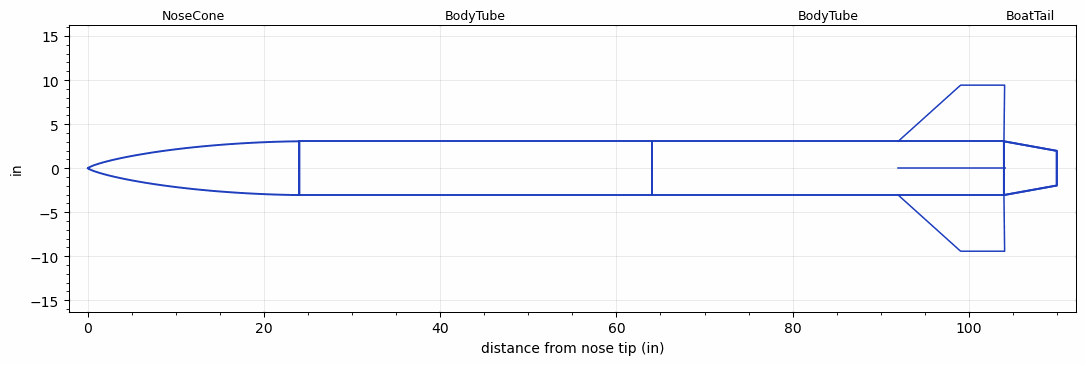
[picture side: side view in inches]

<RASAeroDocument>
 <FileVersion>2</FileVersion>
 <RocketDesign>
  <NoseCone>
   <Length>24</Length>
   <Diameter>6.1</Diameter>
   <Shape>LV-Haack</Shape>
   <Location>0</Location>
  </NoseCone>
  <BodyTube>
   <Length>40</Length>
   <Diameter>6.1</Diameter>
   <Location>24</Location>
  </BodyTube>
  <BodyTube>
   <Length>40</Length>
   <Diameter>6.1</Diameter>
   <RailGuideDiameter>0.372</RailGuideDiameter>
   <RailGuideHeight>0.078</RailGuideHeight>
   <Location>64</Location>
   <BoattailLength>6</BoattailLength>
   <BoattailRearDiameter>3.937</BoattailRearDiameter>
   <Fin>
    <Count>4</Count>
    <Chord>12.0078</Chord>
    <Span>6.3779</Span>
    <SweepDistance>7.0866</SweepDistance>
    <TipChord>5</TipChord>
    <Thickness>0.25</Thickness>
    <Location>12.0078</Location>
    <AirfoilSection>Single Wedge</AirfoilSection>
   </Fin>
  </BodyTube>
  <BoatTail>
   <Length>6</Length>
   <Diameter>6.1</Diameter>
   <RearDiameter>3.937</RearDiameter>
   <Location>104</Location>
  </BoatTail>
  <Surface>Smooth (Zero Roughness)</Surface>
  <ModifiedBarrowman>False</ModifiedBarrowman>
  <Turbulence>False</Turbulence>
  <UseBooster1>False</UseBooster1>
  <UseBooster2>False</UseBooster2>
 </RocketDesign>
 <LaunchSite>
  <Altitude>4595</Altitude>
  <Pressure>24.76</Pressure>
  <RodAngle>6</RodAngle>
  <RodLength>2.2</RodLength>
  <Temperature>56.84</Temperature>
  <WindSpeed>2.33</WindSpeed>
 </LaunchSite>
 <Recovery>
  <Altitude1>1000</Altitude1>
  <Altitude2>0</Altitude2>
  <DeviceType1>Parachute</DeviceType1>
  <DeviceType2>Parachute</DeviceType2>
  <Event1>True</Event1>
  <Event2>True</Event2>
  <Size1>24</Size1>
  <Size2>120</Size2>
  <EventType1>Apogee</EventType1>
  <EventType2>Apogee</EventType2>
  <CD1>0.97</CD1>
  <CD2>2.2</CD2>
 </Recovery>
 <MachAlt>
  <Item>0.02, 1980</Item>
  <Item>0.03, 1977</Item>
  <Item>0.04, 1</Item>
  <Item>0.04, 1973</Item>
  <Item>0.05, 1968</Item>
  <Item>0.06, 2</Item>
  <Item>0.06, 1963</Item>
  <Item>0.07, 3</Item>
  <Item>0.07, 1956</Item>
  <Item>0.08, 4</Item>
  <Item>0.08, 1947</Item>
  <Item>0.09, 1937</Item>
  <Item>0.1, 5</Item>
  <Item>0.1, 1928</Item>
  <Item>0.11, 1916</Item>
  <Item>0.12, 8</Item>
  <Item>0.12, 1903</Item>
  <Item>0.13, 1890</Item>
  <Item>0.14, 1877</Item>
  <Item>0.15, 1855</Item>
  <Item>0.17, 1828</Item>
  <Item>0.19, 1792</Item>
  <Item>0.2, 1769</Item>
  <Item>0.22, 1748</Item>
  <Item>0.23, 29</Item>
  <Item>0.23, 1726</Item>
  <Item>0.24, 1691</Item>
  <Item>0.25, 33</Item>
  <Item>0.27, 42</Item>
  <Item>0.28, 1622</Item>
  <Item>0.29, 1589</Item>
  <Item>0.32, 57</Item>
  <Item>0.33, 1507</Item>
  <Item>0.34, 1468</Item>
  <Item>0.35, 74</Item>
  <Item>0.36, 1415</Item>
  <Item>0.38, 1384</Item>
  <Item>0.39, 93</Item>
  <Item>0.4, 1332</Item>
  <Item>0.43, 114</Item>
  <Item>0.43, 1270</Item>
  <Item>0.49, 1125</Item>
  <Item>0.52, 1049</Item>
  <Item>0.55, 977</Item>
  <Item>0.56, 215</Item>
  <Item>0.58, 910</Item>
  <Item>0.61, 860</Item>
  <Item>0.63, 296</Item>
  <Item>0.63, 821</Item>
  <Item>0.66, 756</Item>
  <Item>0.69, 688</Item>
  <Item>0.71, 409</Item>
  <Item>0.72, 605</Item>
  <Item>0.73, 470</Item>
  <Item>0.73, 532</Item>
 </MachAlt>
 <SimulationList>
  <Simulation>
   <SustainerEngine>M1850W  (Aerotech)</SustainerEngine>
   <SustainerLaunchWt>47.52</SustainerLaunchWt>
   <SustainerNozzleDiameter>2.992</SustainerNozzleDiameter>
   <SustainerCG>64.56</SustainerCG>
   <SustainerIgnitionDelay>0</SustainerIgnitionDelay>
   <Booster1SeparationDelay>0</Booster1SeparationDelay>
   <Booster1IgnitionDelay>0</Booster1IgnitionDelay>
   <IncludeBooster1>False</IncludeBooster1>
   <Booster2Delay>0</Booster2Delay>
   <IncludeBooster2>False</IncludeBooster2>
   <TimetoApogee>29.55058</TimetoApogee>
   <MaxAltitude>14997.7</MaxAltitude>
   <MaxVelocity>1145.965</MaxVelocity>
   <OptimumWt>22.57201</OptimumWt>
   <OptimumMaxAlt>22.57201</OptimumMaxAlt>
  </Simulation>
 </SimulationList>
</RASAeroDocument>
